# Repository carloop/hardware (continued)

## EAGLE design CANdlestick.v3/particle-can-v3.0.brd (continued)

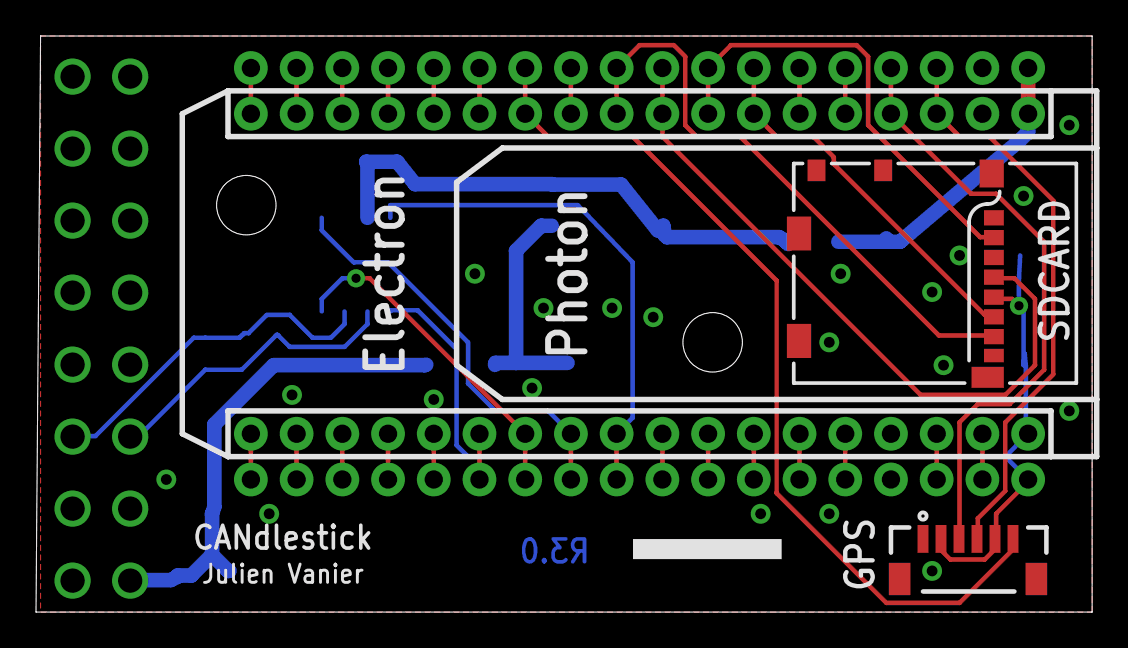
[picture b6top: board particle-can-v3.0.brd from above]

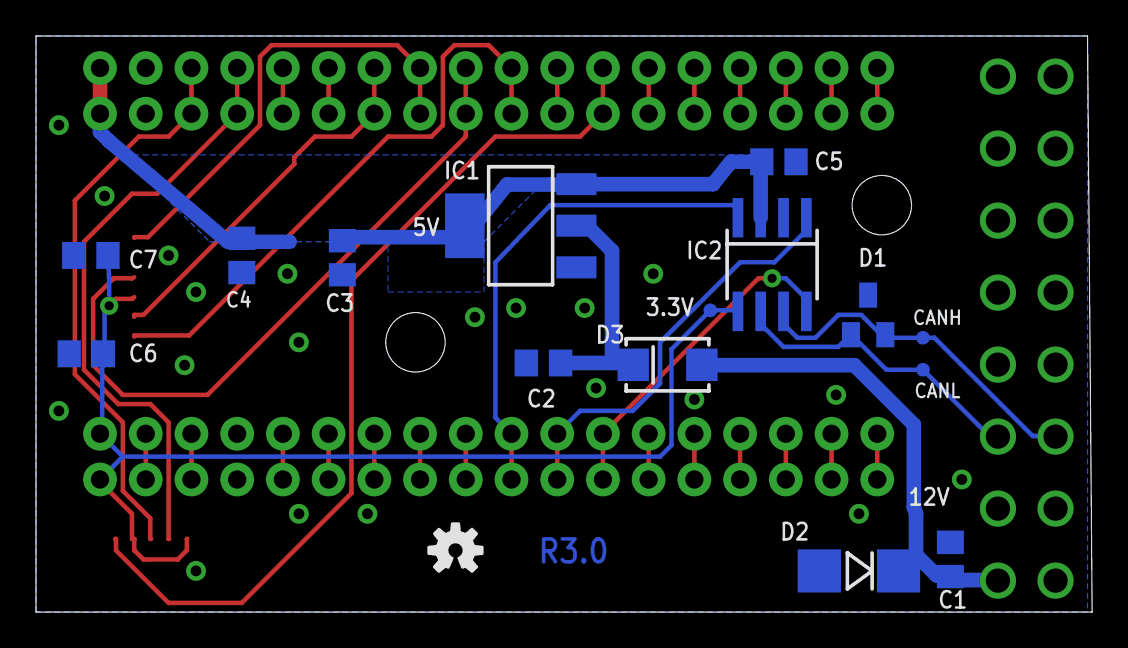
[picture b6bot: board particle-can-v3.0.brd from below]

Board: 2 copper layers, 58.7 x 32.0 mm, 24 parts (17 on the bottom side), 39 nets.

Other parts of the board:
F2: OSHW-LOGO-S
ZDRAW1: A4L-LOC

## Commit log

2016-01-12 Add revision 1.1 design files and images
2016-01-13 fixes typo to make BOM 'beautiful and searchable'
2016-01-25 Revision 2: smaller transceiver, simpler power, GPS
2016-01-27 Version 2 of the PCB has optimized components and GPS
2016-01-28 Revision 3 has the PCB extending outward and SD card
2016-02-01 Revision 3 grows outward (different form factor)
2016-02-15 Update Readme to show V3 schematics
2016-02-23 Revision 2.1 and 3.1
2016-02-24 Add schematic for R2.1
2016-03-28 Carloop PCB revision 2.2
    - Flip the GPS connector landing pattern
    - Add 2nd header to BOM
2016-05-27 Carloop R2.3 with switching power supply
2016-05-31 Add BOM and Gerber files for Rev 2.3
2016-09-21 updated Software text
    updated software content
2016-09-21 updated Carloop pictures
2016-09-21 updated PCB picture
2016-09-21 fixed image size
2016-09-21 updated Carloop picture
2016-09-21 uploaded Photon Pinout
2016-09-21 deleted file
2016-09-21 added smaller sized Photon pinout
2016-09-21 fixed GPS RX/TX typo on Pinout image
2016-09-21 updated Photon pinout picture and links
2016-09-21 styling tweak
2016-09-21 fixed small design issue
2016-09-21 replaced with correct version
2016-09-21 updated links to pics
2016-10-10 Rename schematic files to Carloop
2017-01-14 fixed Carloop-v2-1.pdf link
2017-02-10 Add files via upload
    Add datasheet for K-Line Transceiver IC L9637 from ST Microelectronics.
2017-02-10 Add files via upload
    Schematic with K-Line Transceiver added, based on Carloop.v3.1 design.
    Board Layout is not completed.
2017-02-10 Rename CarloopRetro-v0.1.brd to CarloopRetro-v0/CarloopRetro-v0.1.brd
    Placing file in correct folder structure
2017-02-10 Rename CarloopRetro-v0/CarloopRetro-v0.1.brd to CarloopRetro.v0/CarloopRetro-v0.1.brd
    Placing file in correct folder structure
2017-02-10 Rename CarloopRetro-v0.1.sch to CarloopRetro.v0/CarloopRetro-v0.1.sch
    Place file in correct folder structure
2017-02-11 Update layout PDF links
2017-02-20 Update variants
2017-03-16 v2.3 schematics
2017-03-25 Make layers visible by default
2017-03-31 Remove tool log
2017-04-20 Add draft of GPS shield
2017-04-26 Add GPS_EN
2017-04-26 uploaded Carloop logo
2017-05-08 Tweaks for silkscreen
2017-07-29 added carloop basic image
2018-08-29 Draft of Carloop2
2018-08-29 First prototype of Carloop 2
2018-11-13 Fix PCB bugs
2018-11-13 Add prototype of Carloop Stick
2019-07-07 Update GPS shield schematic
